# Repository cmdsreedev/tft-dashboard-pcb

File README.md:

# ESP32 TFT Dashboard PCB

A compact two-layer carrier board for building a small ESP32-based dashboard. It connects a 30-pin ESP32 development board to an SPI TFT display and a five-pin rotary encoder, with four M2 mounting holes for mechanical assembly.

> **Project status:** Hardware design / first-revision prototype. Review the connector orientation and module pinouts against your exact ESP32 and TFT modules before fabrication or assembly.

## Features

- Socketed 30-pin ESP32 development board
- 11-pin SPI TFT display connection
- Five-pin JST-XH rotary encoder connection
- Bottom-layer ground plane
- Four non-plated 2.2 mm mounting holes for M2 hardware
- Through-hole construction for straightforward hand assembly
- KiCad source files and FreeCAD mechanical models

## Board specification

| Property | Value |
| --- | --- |
| Board size | 79.2 × 54.46 mm |
| Layers | 2 |
| Substrate | FR-4 |
| Thickness | 1.6 mm |
| Copper weight | 1 oz / 35 µm |
| Signal trace width | 0.25 mm |
| Power trace width | 0.56 mm |
| Mounting holes | 4 × 2.2 mm NPTH |

## Interfaces

### TFT display

The display header carries 3V3, GND, backlight, clock, serial data, data/command, reset, and chip-select signals. The PCB silkscreen identifies pin 1 and the power connections.

### Rotary encoder

The JST-XH connector carries `ENC_CLK`, `ENC_DT`, `ENC_SW`, `3V3`, and `GND`.

## Repository contents

- `tft-design.kicad_pro` — main KiCad project
- `tft-design.kicad_sch` — schematic
- `tft-design.kicad_pcb` — PCB layout
- `tft-design.FCStd` — FreeCAD mechanical model
- `tft-design_resized.FCStd` — alternate/resized mechanical model
- `1.kicad_pro` and `1.kicad_pcb` — additional KiCad design files retained with the project

Fabrication outputs are intentionally not tracked. Generate fresh Gerber and drill files from the current PCB revision before ordering.

## Fabrication export

1. Open `tft-design.kicad_pro` in KiCad 10 or a compatible newer release.
2. Open PCB Editor, refill copper zones, and run the Design Rules Checker.
3. Plot `F.Cu`, `B.Cu`, `F.Mask`, `B.Mask`, `F.SilkS`, `B.SilkS`, and `Edge.Cuts` as Gerbers.
4. Generate both PTH and NPTH Excellon drill files.
5. Load every Gerber and both drill files in Gerber Viewer.
6. Confirm the outline, plated connector holes, non-plated mounting holes, copper, and silkscreen before creating the fabrication ZIP.

## Assembly checks

Before powering the board:

- Confirm the ESP32 header orientation and pin-1 positions.
- Confirm the TFT module uses the expected 11-pin ordering.
- Verify that the TFT module includes suitable backlight current limiting, or add an appropriate external driver/current-limiting solution.
- Check for shorts between `3V3` and `GND`.
- Power the board with a current-limited supply for initial bring-up.

## Software

Firmware is not included in this repository. The chosen display driver and GPIO definitions must match the fitted TFT module and the PCB net assignments.

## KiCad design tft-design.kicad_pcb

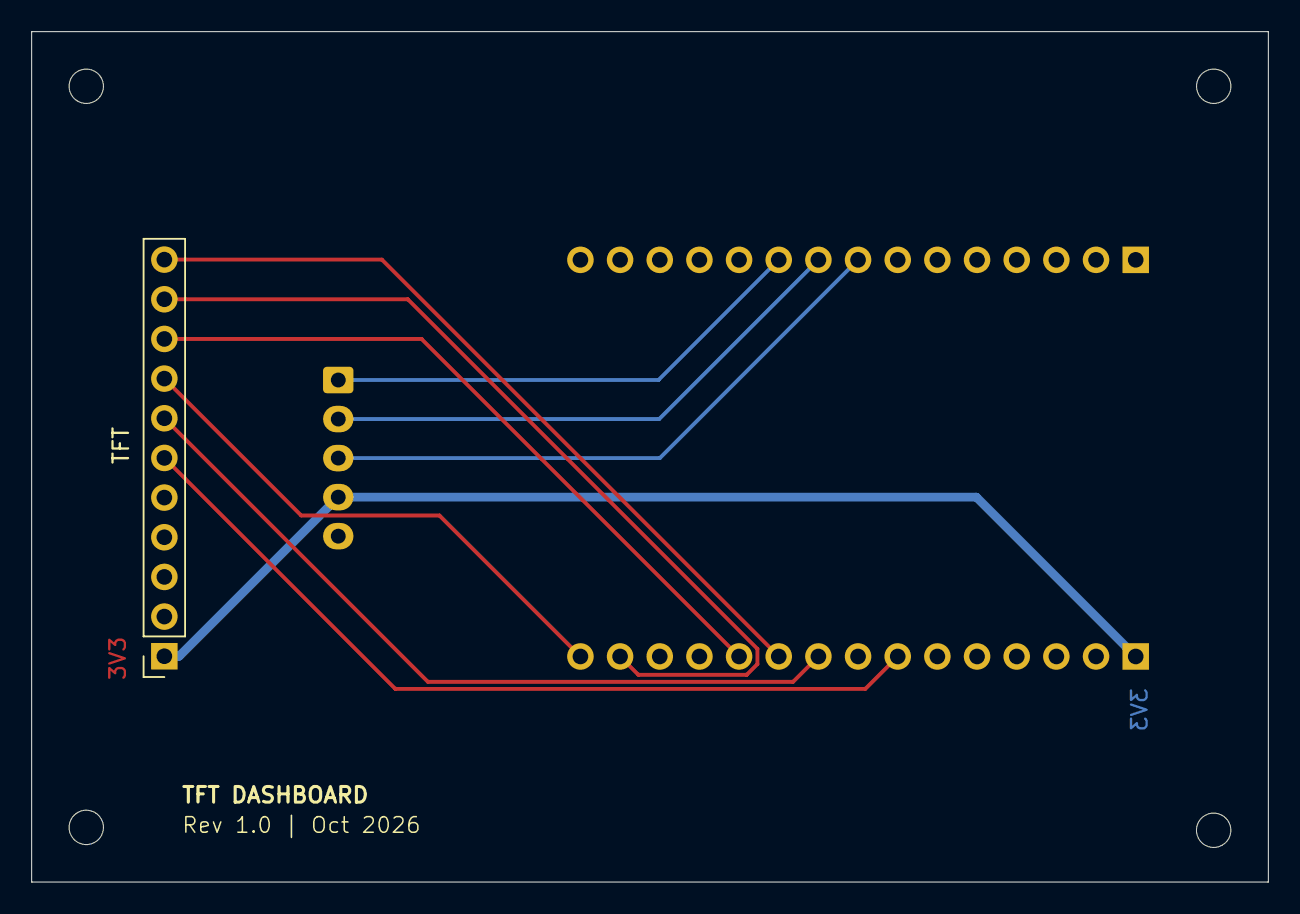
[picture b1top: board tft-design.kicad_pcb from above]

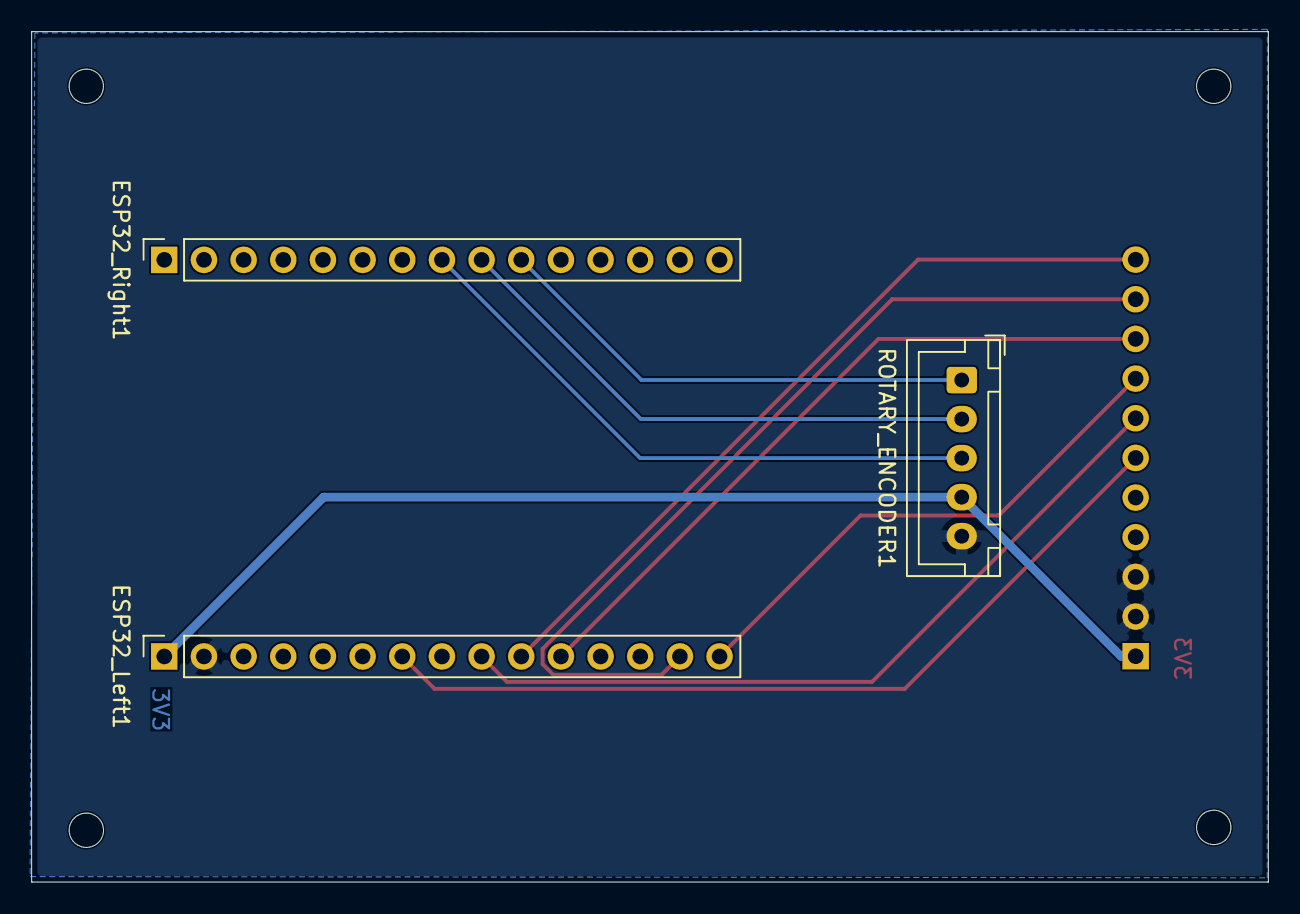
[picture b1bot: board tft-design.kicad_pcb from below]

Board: 2 copper layers, 79.2 x 54.5 mm, 4 parts (3 on the bottom side), 11 nets.

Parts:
ESP32_Left1, ESP32_Right1: Conn_01x15; PinSocket_1x15_P2.54mm_Vertical
ROTARY_ENCODER1: Conn_01x05; JST_XH_B5B-XH-A_1x05_P2.50mm_Vertical
TFT: Conn_01x11; PinSocket_1x11_P2.54mm_Vertical

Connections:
/3V3: ESP32_Left1.1, ROTARY_ENCODER1.4, TFT.1
/ENC_CLK: ESP32_Right1.10, ROTARY_ENCODER1.1
/ENC_DT: ESP32_Right1.9, ROTARY_ENCODER1.2
/ENC_SW: ESP32_Right1.8, ROTARY_ENCODER1.3
/GND: ESP32_Left1.2, ROTARY_ENCODER1.5, TFT.2, TFT.3
/TFT_CLK: ESP32_Left1.9, TFT.7
/TFT_CS: ESP32_Left1.10, TFT.11
/TFT_LED: ESP32_Left1.7, TFT.6
/TFT_RS: ESP32_Left1.11, TFT.9
/TFT_RST: ESP32_Left1.14, TFT.10
/TFT_SDI: ESP32_Left1.15, TFT.8

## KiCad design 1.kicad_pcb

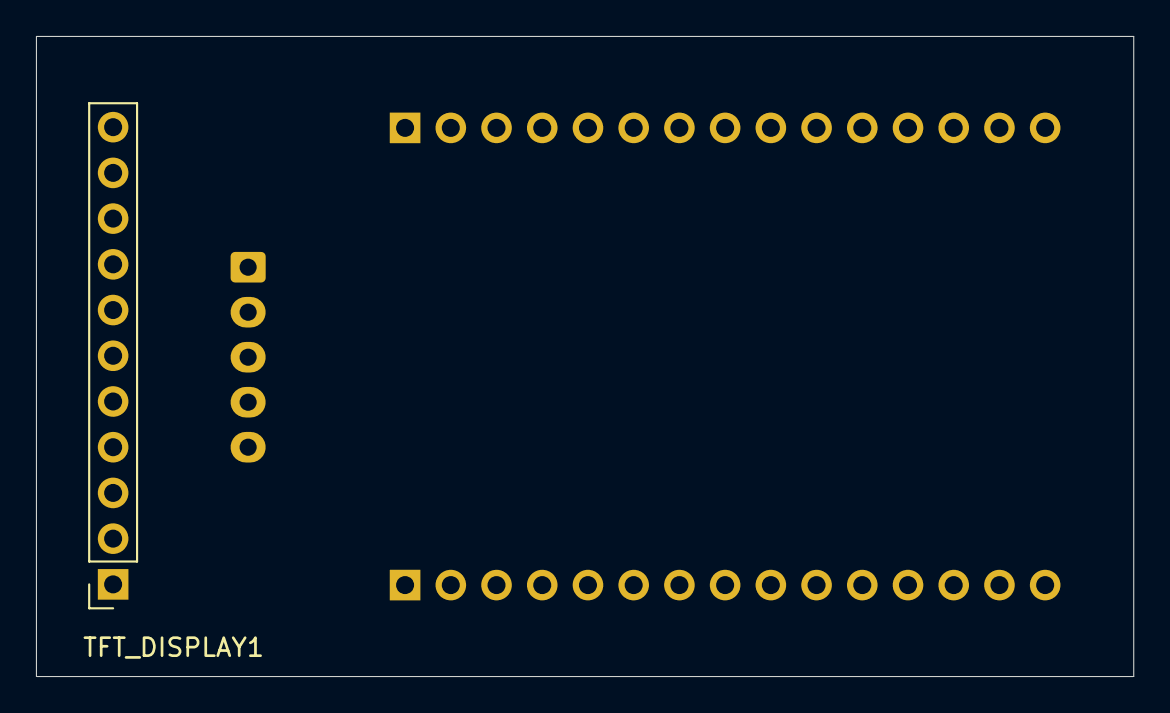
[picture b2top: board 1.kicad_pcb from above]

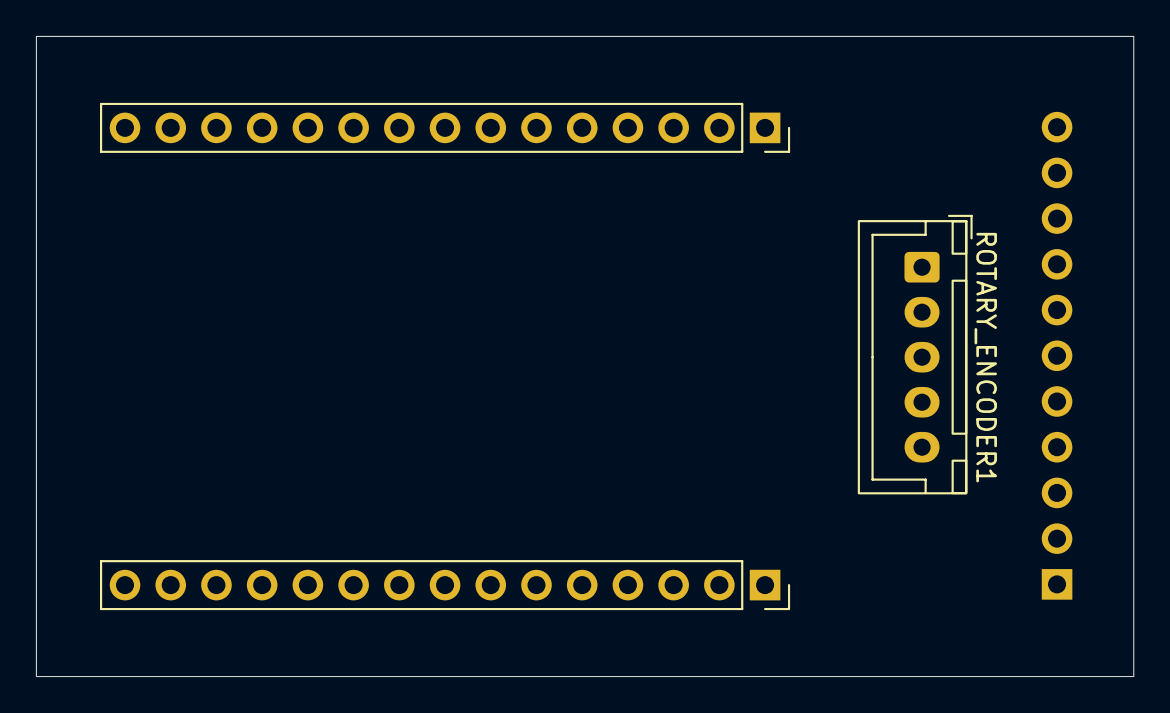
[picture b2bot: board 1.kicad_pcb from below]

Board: 2 copper layers, 61.0 x 35.6 mm, 4 parts (3 on the bottom side), 11 nets, no tracks yet.

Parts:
ESP32_Left1, ESP32_Right1: Conn_01x15; PinSocket_1x15_P2.54mm_Vertical
ROTARY_ENCODER1: Conn_01x05; JST_XH_B5B-XH-A_1x05_P2.50mm_Vertical
TFT_DISPLAY1: Conn_01x11; PinSocket_1x11_P2.54mm_Vertical

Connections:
/3V3: ESP32_Left1.1, ROTARY_ENCODER1.4, TFT_DISPLAY1.1
/ENC_CLK: ESP32_Right1.10, ROTARY_ENCODER1.1
/ENC_DT: ESP32_Right1.9, ROTARY_ENCODER1.2
/ENC_SW: ESP32_Left1.10, ROTARY_ENCODER1.3
/GND: ESP32_Left1.2, ROTARY_ENCODER1.5, TFT_DISPLAY1.2
/TFT_CLK: ESP32_Left1.9, TFT_DISPLAY1.7
/TFT_CS: ESP32_Right1.6, TFT_DISPLAY1.11
/TFT_LED: ESP32_Left1.11, TFT_DISPLAY1.6
/TFT_RS: ESP32_Right1.7, TFT_DISPLAY1.9
/TFT_RST: ESP32_Right1.8, TFT_DISPLAY1.10
/TFT_SDI: ESP32_Left1.15, TFT_DISPLAY1.8
